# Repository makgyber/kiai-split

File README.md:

# Kiai Wireless Split Keyboard

## Features
- Seeed Studio XIAO nRF52840 
- ZMK
- 34-keys 
- low profile Choc v1

## Requirements
- Seeed Studio XIAO nRF52840 (2)
- Choc v1 switche (34)
- 1N4148 SOD-123  (34)
- 2 pcbs (gerbers and kicad files shared in this repo)
- 3.7v lipo batteries (2)

## Build Notes
Because I wanted to have the xiao modules both facing up so the built-in reset button on the xiao is readily accessible, there are a couple of things that may be different from how other boards are normally set up.

For the left hand side, need to jumper the bottom two holes as shown below:

The right side will also need the jumper but on the upper two holes instead:

The diodes should mirror the orientation on the opposite board.

## Flashing the Firmware
For convenience, the compiled uf2 files are in the bin folder. 
`left.uf2` -> for the left side
`right.uf2` -> for the right side
`reset.uf2` -> can be flashed to both boards to reset. I found this useful when the slave side is not pairing with the master side.

### How to upload the firmware to your board:
- Connect one keyboard to your computer via USB 
- Double-click the reset button on the xiao module on the left board. When the XIAO-SENSE folder appears, copy over `left.uf2` onto that folder. It will automatically eject after.
- Do the same to the right keyboard, this time flashing the `right.uf2` file.
- TIP: immediately after flashing try to put the keyboard into bootloader mode. This prevents it from trying to pair before you are ready. Re-activate the two sides at the same time; this usually helps when you find the slave side does not register keystrokes. 

## Building/Compiling your own firmware

- install ZMK following this guide: [ZMK Basic Setup](https://zmk.dev/docs/development/setup) 
- in your `{zmk-dir}/app/board/shields` directory, create a folder named `kiai`
- copy the files in the `zmk` folder in this repo into your new `kiai` directory
- compile the hex file for your left board using 
  
  ```west build -p -b seeeduino_xiai_ble -d build/kiai/left -- -DSHIELD=kiai_left```
- this will create a `zmk.uf2` file in `{zmk-dir}/app/build/kiai/left/zephyr`
- use this file to flash the left-side board
- compile the hex file for your right-side board using
  
  ```west build -p -b seeeduino_xiai_ble -d build/kiai/right -- -DSHIELD=kiai_right```

- this will create a `zmk.uf2` file in `{zmk-dir}/app/build/kiai/right/zephyr`
- use this file to flash the right-side board

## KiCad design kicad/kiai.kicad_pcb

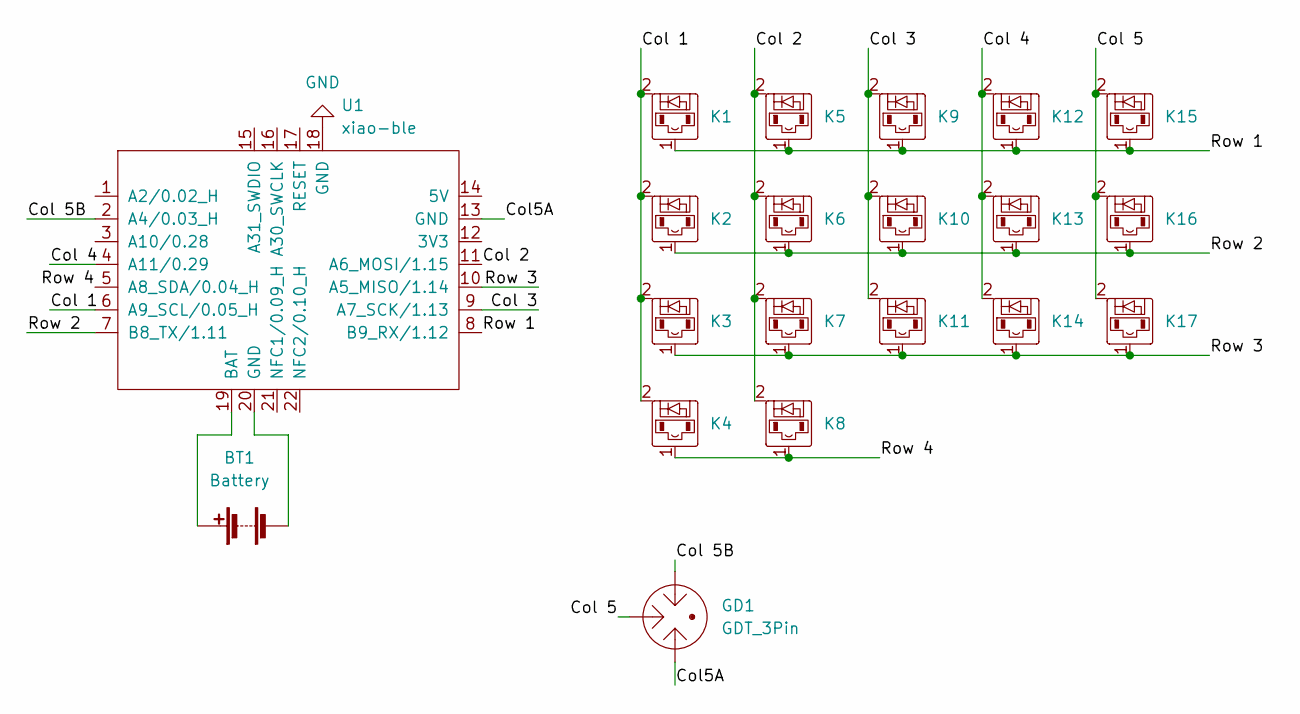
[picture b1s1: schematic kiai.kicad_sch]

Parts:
BT1: Battery; JST_EH_B2B-EH-A_1x02_P2.50mm_Vertical
GD1: GDT_3Pin; PinHeader_1x03_P1.00mm_Vertical
K1, K2, K3, K4, K5, K6, K7, K8, K9, K10, K11, K12, K13, K14, K15, K16, K17: diode-choc; pg1350-DR
U1: xiao-ble; xiao-ble-tht

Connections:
/Col5A: GD1.1, U1.13 (GND)
/Col 1: K1.2, K2.2, K3.2, K4.2, U1.6 (A9_SCL/0.05_H)
/Col 2: K5.2, K6.2, K7.2, K8.2, U1.11 (A6_MOSI/1.15)
/Col 3: K9.2, K10.2, K11.2, U1.9 (A7_SCK/1.13)
/Col 4: K12.2, K13.2, K14.2, U1.4 (A11/0.29)
/Col 5: GD1.2, K15.2, K16.2, K17.2
/Col 5B: GD1.3, U1.2 (A4/0.03_H)
/Row 1: K1.1, K5.1, K9.1, K12.1, K15.1, U1.8 (B9_RX/1.12)
/Row 2: K2.1, K6.1, K10.1, K13.1, K16.1, U1.7 (B8_TX/1.11)
/Row 3: K3.1, K7.1, K11.1, K14.1, K17.1, U1.10 (A5_MISO/1.14)
/Row 4: K4.1, K8.1, U1.5 (A8_SDA/0.04_H)
GND: U1.18 (GND)
unnamed: BT1.1 (+), U1.19 (BAT)
unnamed: BT1.2 (-), U1.20 (GND)

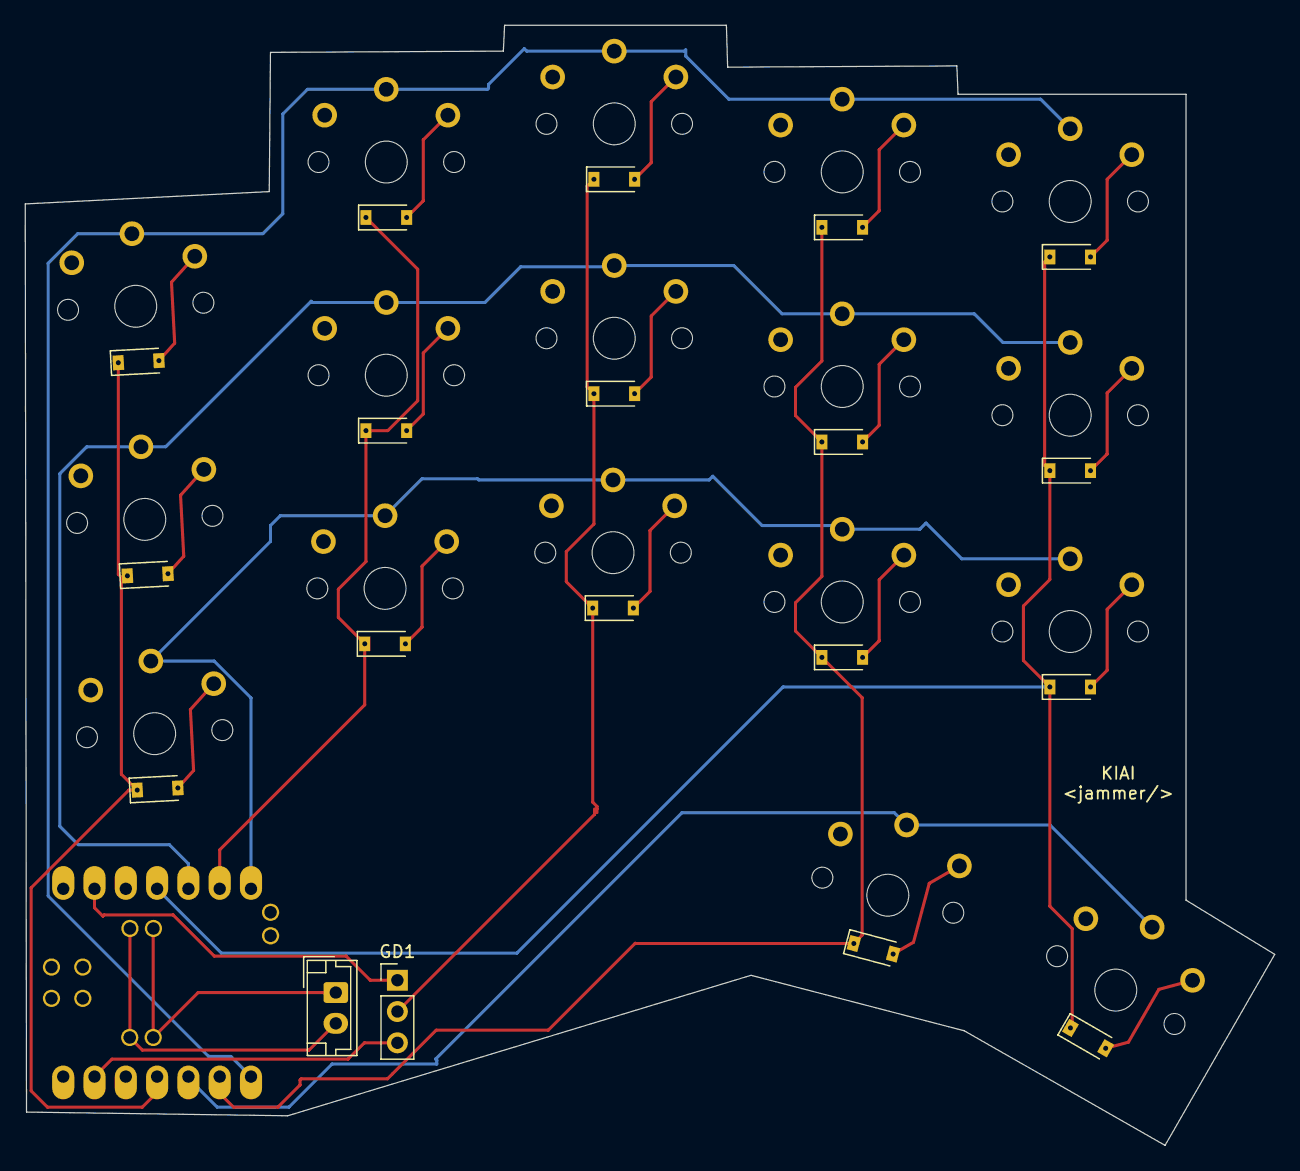
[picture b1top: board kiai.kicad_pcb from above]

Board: 2 copper layers, 101.4 x 90.9 mm, 20 parts (0 on the bottom side), 13 nets.

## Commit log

2022-11-18 revert
2022-11-18 update keymap
2022-11-19 docs and images
2022-11-25 update board image
2022-11-25 new higher-res image
2022-11-25 added views
2022-11-28 updated the binaries
2023-01-02 update readme with diode orientation pics
2023-01-20 updated keymap
